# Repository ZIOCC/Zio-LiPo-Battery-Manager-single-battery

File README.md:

# Zio LiPo Battery Manager (Single battery)

> This product can be available for purchase [here](https://www.smart-prototyping.com/Zio-LiPo-Battery-Manager.html).

#### Description

This board combines a lithium polymer battery charger, fuel gauge, and voltage regulator, all in one neat little PCB. It also features a miniature DPDT power switch so that you can easily turn your project on and off without disconnecting the battery.

The Battery Manager’s TI BQ27441-G1A I2C Fuel Gauge is a Coulomb-counter, tracking the amount of power that has been discharged since your battery was fully charged. The amount of power remaining is calculated based on the capacity of that battery that you’ve set via the [Sparkfun BQ27441-G1 I2C library](https://learn.sparkfun.com/tutorials/battery-babysitter-hookup-guide#bq27441-arduino-library). Using the library, you can also read the raw voltage of your LiPo battery’s output. And because this is a Qwiic device, your MCU can check this information even if your battery and Battery Manager board are all the way at the other end of your daisy-chain of Qwiic modules. And if your Power Module is close to your MCU, just connect the GPOUT interrupt pin to one of your MCU’s GPIO pins to get a heads-up when the tank is running low. And because of the built-in current-sensing resistor circuit, you can even measure your project’s real-time current consumption.

The Battery Manager’s BQ24075 battery charger IC can charge your single-cell lithium-ion battery pack at up to 1.5A.

Our Battery Manager board is based on [Sparkfun’s Battery Babysitter](https://www.sparkfun.com/products/13777), and while the pin-out isn’t exactly the same, their [Hookup Guide](https://learn.sparkfun.com/tutorials/battery-babysitter-hookup-guide) is a great resource for getting started with our board as well.

Note: This board requires the use of the Qwiic (4-pin JST-SH) connector for accessing the I2C functionality of the BQ27441-G1A. If you intend to use this board in a project where your MCU doesn’t include a Qwiic connector, make sure you pick up a [Qwiic-to-breadboard cable](https://www.smart-prototyping.com/Prototyping-Modules/zio/Qwiic-to-Breadboard-Male-Header-150mm-Cable-2.54mm-10pcs), or any [Qwiic cable](https://www.smart-prototyping.com/index.php?route=product/search&search=qwiic%20cable) and a [Qwiic adapter board](https://www.smart-prototyping.com/Prototyping-Modules/zio/Zio-Qwiic-Adapter.html).

##### Features

* Protects the battery from running outside the safe operating area.
* Easy to connect to any ZIO products with one simple Qwiic cable.
* Features a dynamic power-path management which will maintain a solid output supply of 3.3V
* Contains a safety timer which will turn off the charger after 6.25 hours.

#### Specification

* Input Voltage- 6V max
* Output Voltage- 3.3V
* Output current- 1.5A max
* Qwiic connectors 3.3v and 1.5A max
* Battery Connector: PH Connector
* Battery Charger IC: BQ24075
* Power Manager IC: TPS63020DSJR
* Battery Gauge IC: BQ27441-G1
* I2C address:0x55
* Dimensions: 32.23x 33.24 mm
* Weight: 4.9g

#### Links

* [Eagle files](https://github.com/ZIOCC/Zio-LiPo-Battery-Manager-single-battery/tree/master/EAGLE)

> ###### About Zio
> Zio is a new line of open sourced, compact, and grid layout boards, fully integrated for Arduino and Qwiic ecosystem. Designed ideally for wearables, robotics, small-space limitations or other on the go projects. Check out other awesome Zio products [here](https://www.smart-prototyping.com/Zio).

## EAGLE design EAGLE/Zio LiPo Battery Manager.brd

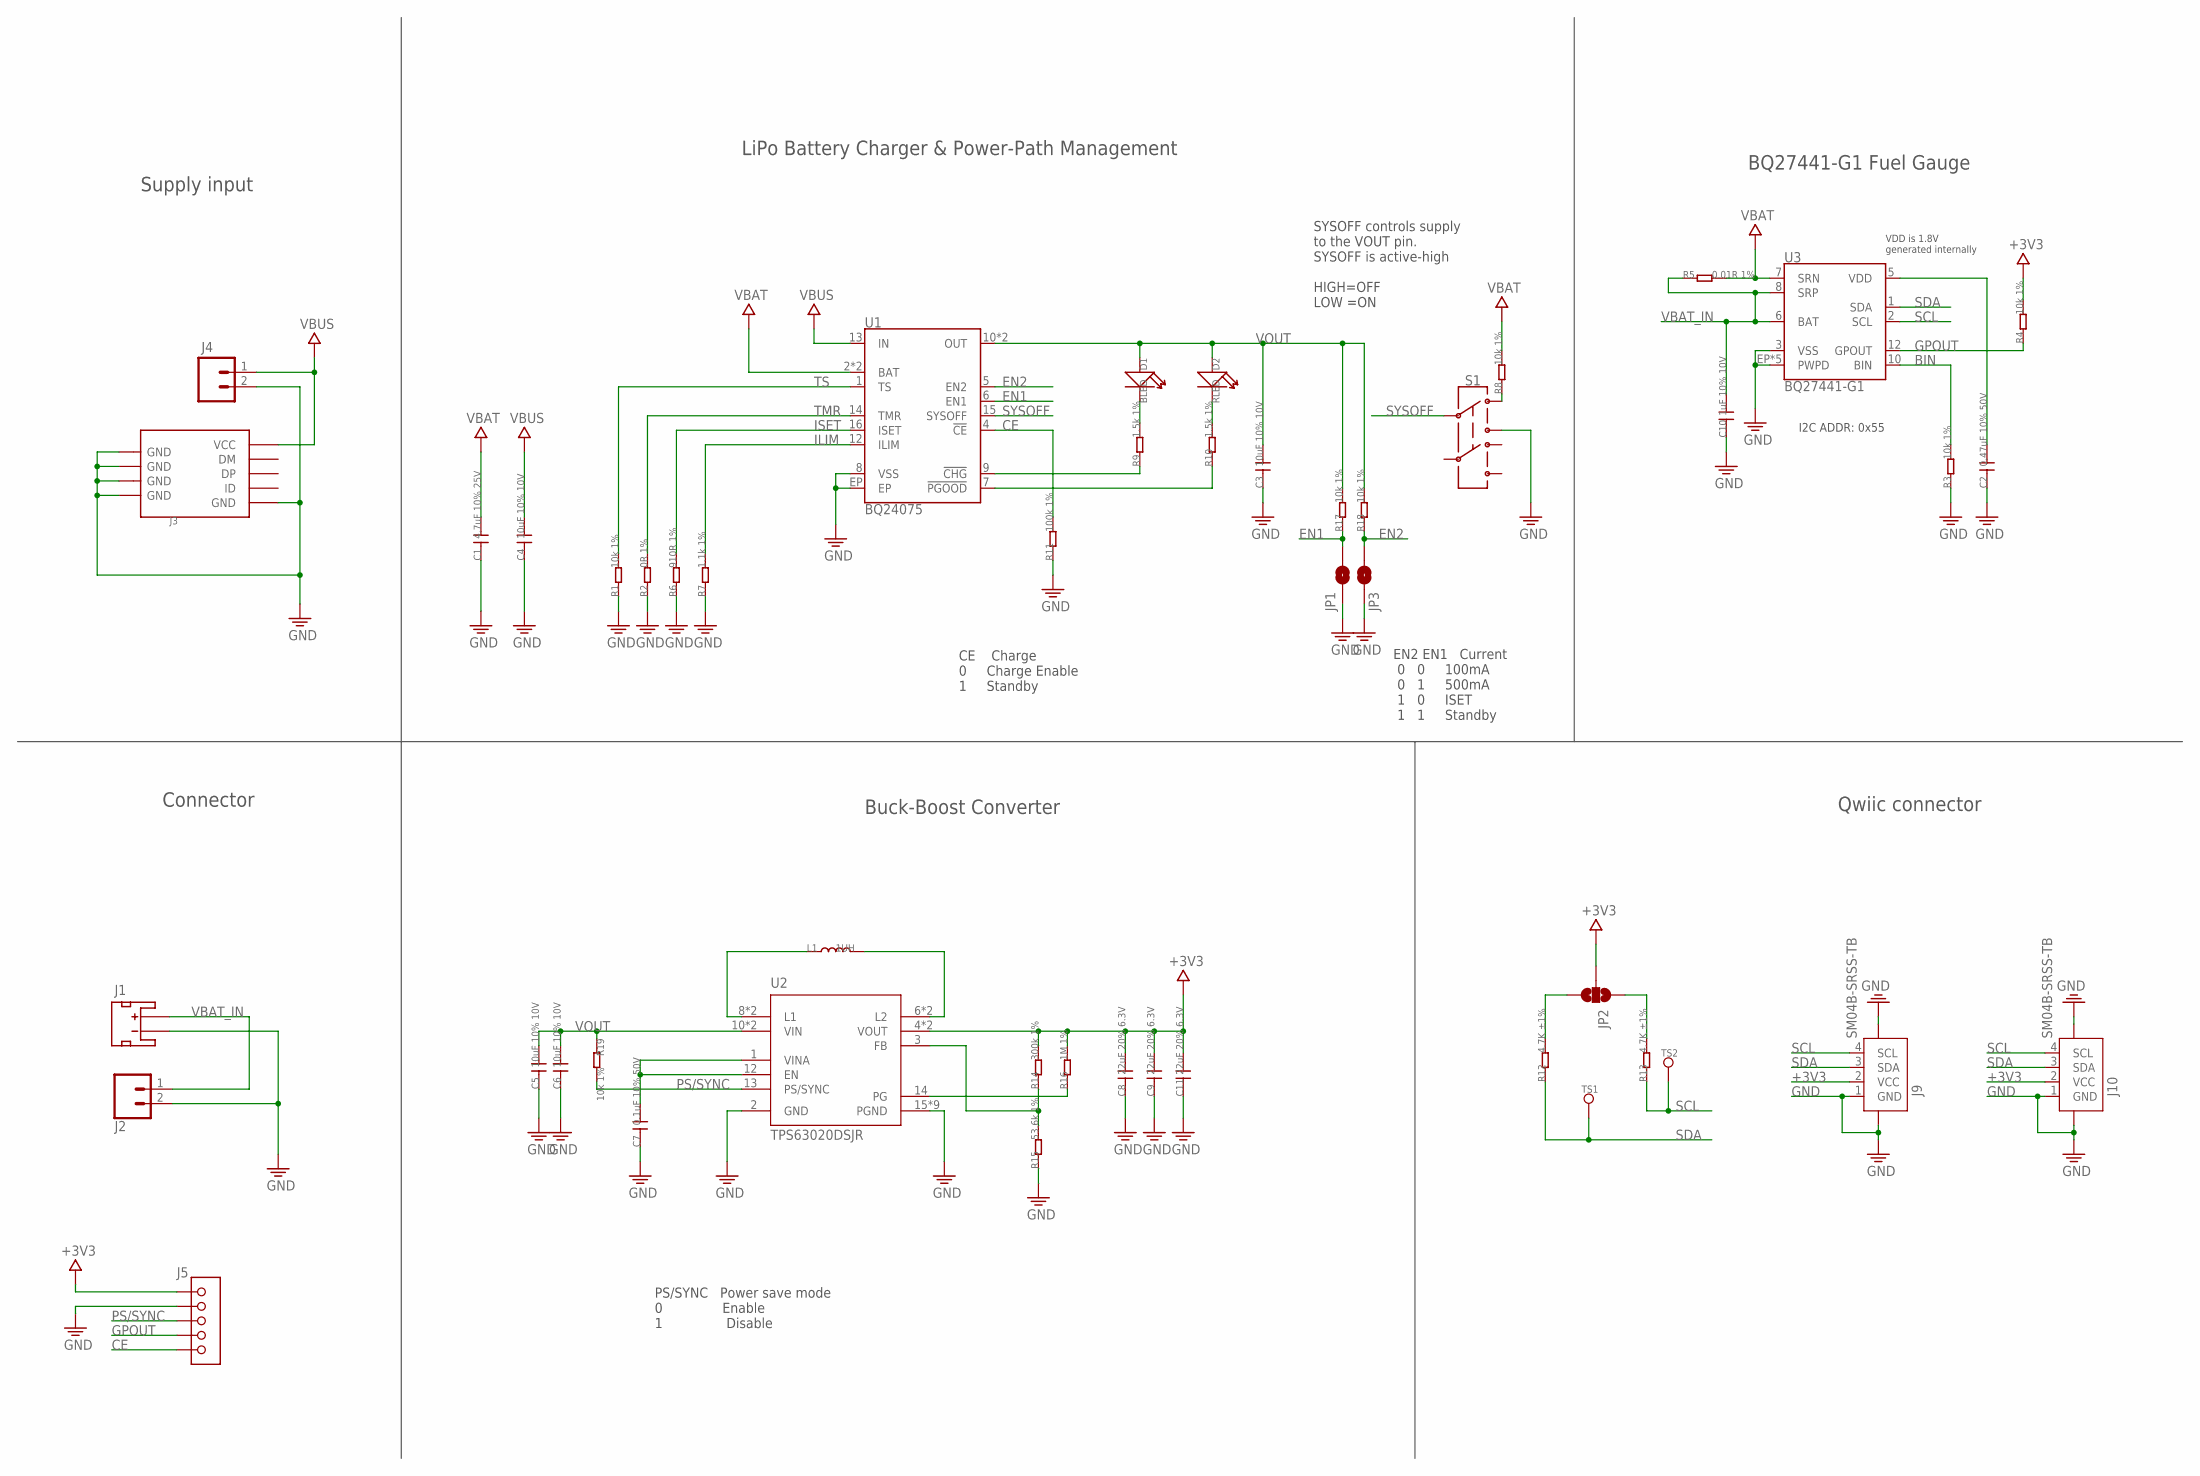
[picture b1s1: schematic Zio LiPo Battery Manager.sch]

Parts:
C1: 4.7uF 10% 25V; 0603
C2: 0.47uF 10% 50V; 0603
C3, C4, C5, C6: 10uF 10% 10V; 0805
C7: 0.1uF 10% 50V; 0603
C8, C9, C11: 22uF 20% 6.3V; 0805
C10: 1uF 10% 10V; 0603
D1: BLED; LED-0603
D2: RLED; LED-0603
J1: JST_2MM_MALE; JST-2-SMD
J2, J4: CONN_02; 1X02
J3: USB-MICROE; MICRO-SMD
J5: HEADER-5P-2.54; 5P-2.54
J9, J10: SM04B-SRSS-TB; JST-SH-4P
JP1, JP3: JUMPER-SMT_2_NC_PASTE_NOCREM; SMT-JUMPER_2_NC_PASTE_SILK_NOCREM
JP2: JUMPER-SMT_3_2-NC_PASTE_NOCREM; SMT-JUMPER_3_2-NC_PASTE_SILK_NOCREM
L1: 1UH; 0420M
R1, R3, R4, R8, R17, R18, R19: 10k 1%; 0603
R2: 0R 1%; 0603
R5: 0.01R 1%; 1206
R6: 910R 1%; 0603
R7: 1.1k 1%; 0603
R9, R10: 1.5k 1%; 0603
R11: 100k 1%; 0603
R12, R13: 4.7K ±1%; 0603
R14: 300k 1%; 0603
R15: 53.6k 1%; 0603
R16: 1M 1%; 0603
S1: SWITCH-DPDT-SMD-AYZ0202; SWITCH_DPDT_SMD_AYZ0202
TS1, TS2: TEST_POINT35MIL; 1P-35MIL
U1: BQ24075; PVQFN-N16
U2: TPS63020DSJR; VSON-14
U3: BQ27441-G1; PDSO-N12

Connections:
1.8V: C2.2, U3.5 (VDD)
+3V3: C8.2, C9.2, C11.2, J5.1, J9.2 (VCC), J10.2 (VCC), JP2.2, R4.2, R14.2, R16.2, U2.4 (VOUT), U2.5 (VOUT)
BIN: R3.2, U3.10 (BIN)
CE: J5.5, R11.2, U1.4 (!CE!)
EN1: JP1.2, R17.1, U1.6 (EN1)
EN2: JP3.2, R18.1, U1.5 (EN2)
GND: C1.1, C2.1, C3.1, C4.1, C5.1, C6.1, C7.1, C8.1, C9.1, C10.1, C11.1, J1.1 (-), J2.2, J3.GND, J3.S1 (GND), J3.S1@1 (GND), J3.S1@2 (GND), J3.S2 (GND), J3.S2@1 (GND), J3.S2@2 (GND), J3.S3 (GND), J3.S3@1 (GND), J3.S3@2 (GND), J3.S4 (GND), J3.S4@1 (GND), J3.S4@2 (GND), J4.2, J5.2, J9.1 (GND), J9.NC1 (5), J9.NC2 (6), J10.1 (GND), J10.NC1 (5), J10.NC2 (6), JP1.1, JP3.1, R1.1, R2.1, R3.1, R6.1, R7.1, R11.1, R15.1, S1.3, U1.8 (VSS), U1.EP, U2.2 (GND), U2.15 (PGND), U2.16 (PGND), U2.17 (PGND), U2.18 (PGND), U2.19 (PGND), U2.20 (PGND), U2.21 (PGND), U2.22 (PGND), U2.23 (PGND), U3.3 (VSS), U3.EP (PWPD), U3.EP1 (PWPD), U3.EP2 (PWPD), U3.EP3 (PWPD), U3.EP4 (PWPD)
GPOUT: J5.4, R4.1, U3.12 (GPOUT)
ILIM: R7.2, U1.12 (ILIM)
ISET: R6.2, U1.16 (ISET)
unnamed: JP2.3, R12.2
unnamed: C7.2, U2.1 (VINA), U2.12 (EN)
unnamed: R8.1, S1.1
unnamed: R9.1, U1.9 (!CHG!)
unnamed: R14.1, R15.2, U2.3 (FB)
unnamed: D1.-, R9.2
unnamed: JP2.1, R13.2
unnamed: R10.1, U1.7 (!PGOOD!)
unnamed: D2.-, R10.2
unnamed: L1.1, U2.8 (L1), U2.9 (L1)
unnamed: L1.2, U2.6 (L2), U2.7 (L2)
PG: R16.1, U2.14 (PG)
PS/SYNC: J5.3, R19.2, U2.13 (PS/SYNC)
SCL: J9.4 (SCL), J10.4 (SCL), R13.1, TS2.P$1, U3.2 (SCL)
SDA: J9.3 (SDA), J10.3 (SDA), R12.1, TS1.P$1, U3.1 (SDA)
SYSOFF: S1.2, U1.15 (SYSOFF)
TMR: R2.2, U1.14 (TMR)
TS: R1.2, U1.1 (TS)
VBAT: C1.2, R5.2, R8.2, U1.2 (BAT), U1.3 (BAT), U3.7 (SRN)
VBAT_IN: C10.2, J1.2 (+), J2.1, R5.1, U3.6 (BAT), U3.8 (SRP)
VBUS: C4.2, J3.VBUS (VCC), J4.1, U1.13 (IN)
VOUT: C3.2, C5.2, C6.2, D1.+, D2.+, R17.2, R18.2, R19.1, U1.10 (OUT), U1.11 (OUT), U2.10 (VIN), U2.11 (VIN)

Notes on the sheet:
BQ27441-G1 Fuel Gauge
LiPo Battery Charger & Power-Path Management
Qwiic connector
VDD is 1.8V generated internally
I2C ADDR: 0x55
SYSOFF controls supply to the VOUT pin. SYSOFF is active-high HIGH=OFF LOW =ON
Supply input
Buck-Boost Converter
Connector
EN2 EN1 Current 0 0 100mA 0 1 500mA 1 0 ISET 1 1 Standby
PS/SYNC Power save mode 0 Enable 1 Disable
CE Charge 0 Charge Enable 1 Standby

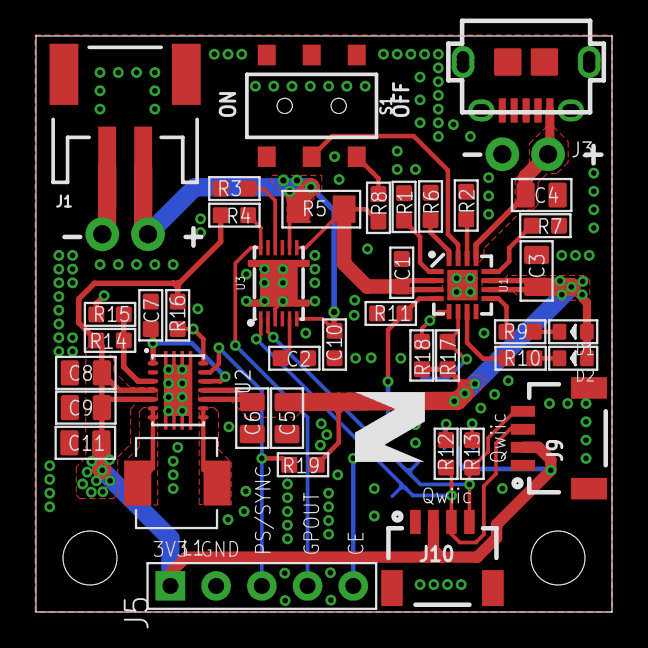
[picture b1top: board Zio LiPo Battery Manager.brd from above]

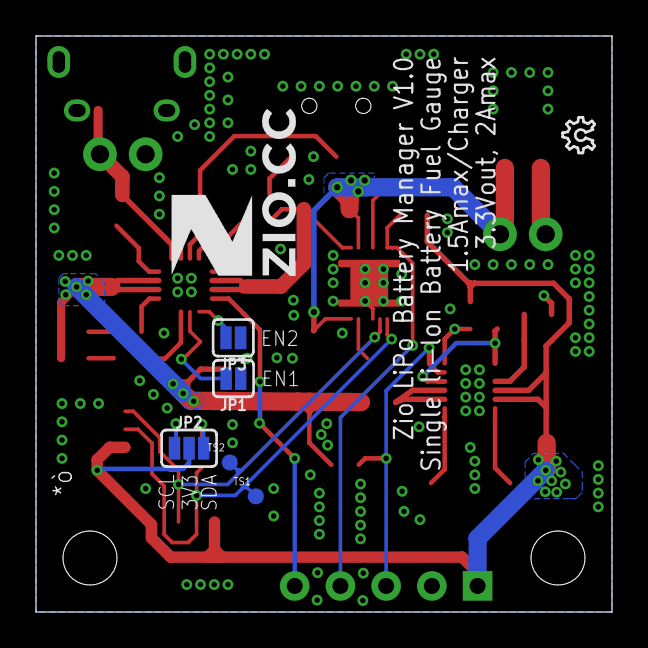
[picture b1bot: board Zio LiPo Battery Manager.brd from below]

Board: 2 copper layers, 32.0 x 32.0 mm, 52 parts (7 on the bottom side), 32 nets.

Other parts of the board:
LOGO1: LOGO-OSHW-6MILX0070-NT; OSHW_6X70_NOTEXT
U$1: 7MM
U$2: 6MM

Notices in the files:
parts and their libraries:
SparkFun-Connectors: Licensing: Creative Commons ShareAlike 4.0 International - https://creativecommons.org/licenses/by-sa/4.0
